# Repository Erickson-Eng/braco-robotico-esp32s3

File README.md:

# Disciplina de prototipagem

Projeto de desenvolvimento de braço róbotico realizado no fusion 360 no qual consiste em criar um braço com uma lâmina acoplada capaz de realizar a manutenção da lavoura fazendo a retirada de fungos e ou também realizar a retirada de algumas frutas como por exemplo a uva.

## Diretorios

- [Arquivos 3D](https://github.com/Erickson-Eng/braco-robotico-esp32s3/tree/main/modelos_3d/componentes-3d)
- [Arquivos F3D](https://github.com/Erickson-Eng/braco-robotico-esp32s3/tree/main/modelos_3d/componentes-f3d)
- [Arquivos STL](https://github.com/Erickson-Eng/braco-robotico-esp32s3/tree/main/modelos_3d/componentes-stl)

## Grupo 7

### Alunos

- Erickson Tulio Rodrigues Azevedo
- Arthur Venancio Furtado Fialho
- Mozart Lima Nascimento

### Professor

- Alexandre Sales Vasconcelos

## Braço robótico

Componentes para construção do braço róbotico.

### Base do braço

### Tampa de conexão entre base e haste

### Haste de conexão com a tampa

### Engrenagem conectora com haste

### Haste de conexão com a lâmina

### Lista de materias

Nome | Referência | Tipo
-----|------------|--------
Stepper Motor | 6627T54 | Motor
Precision Knife Blades | 38995A84_Trade No. 28 | Lâmina

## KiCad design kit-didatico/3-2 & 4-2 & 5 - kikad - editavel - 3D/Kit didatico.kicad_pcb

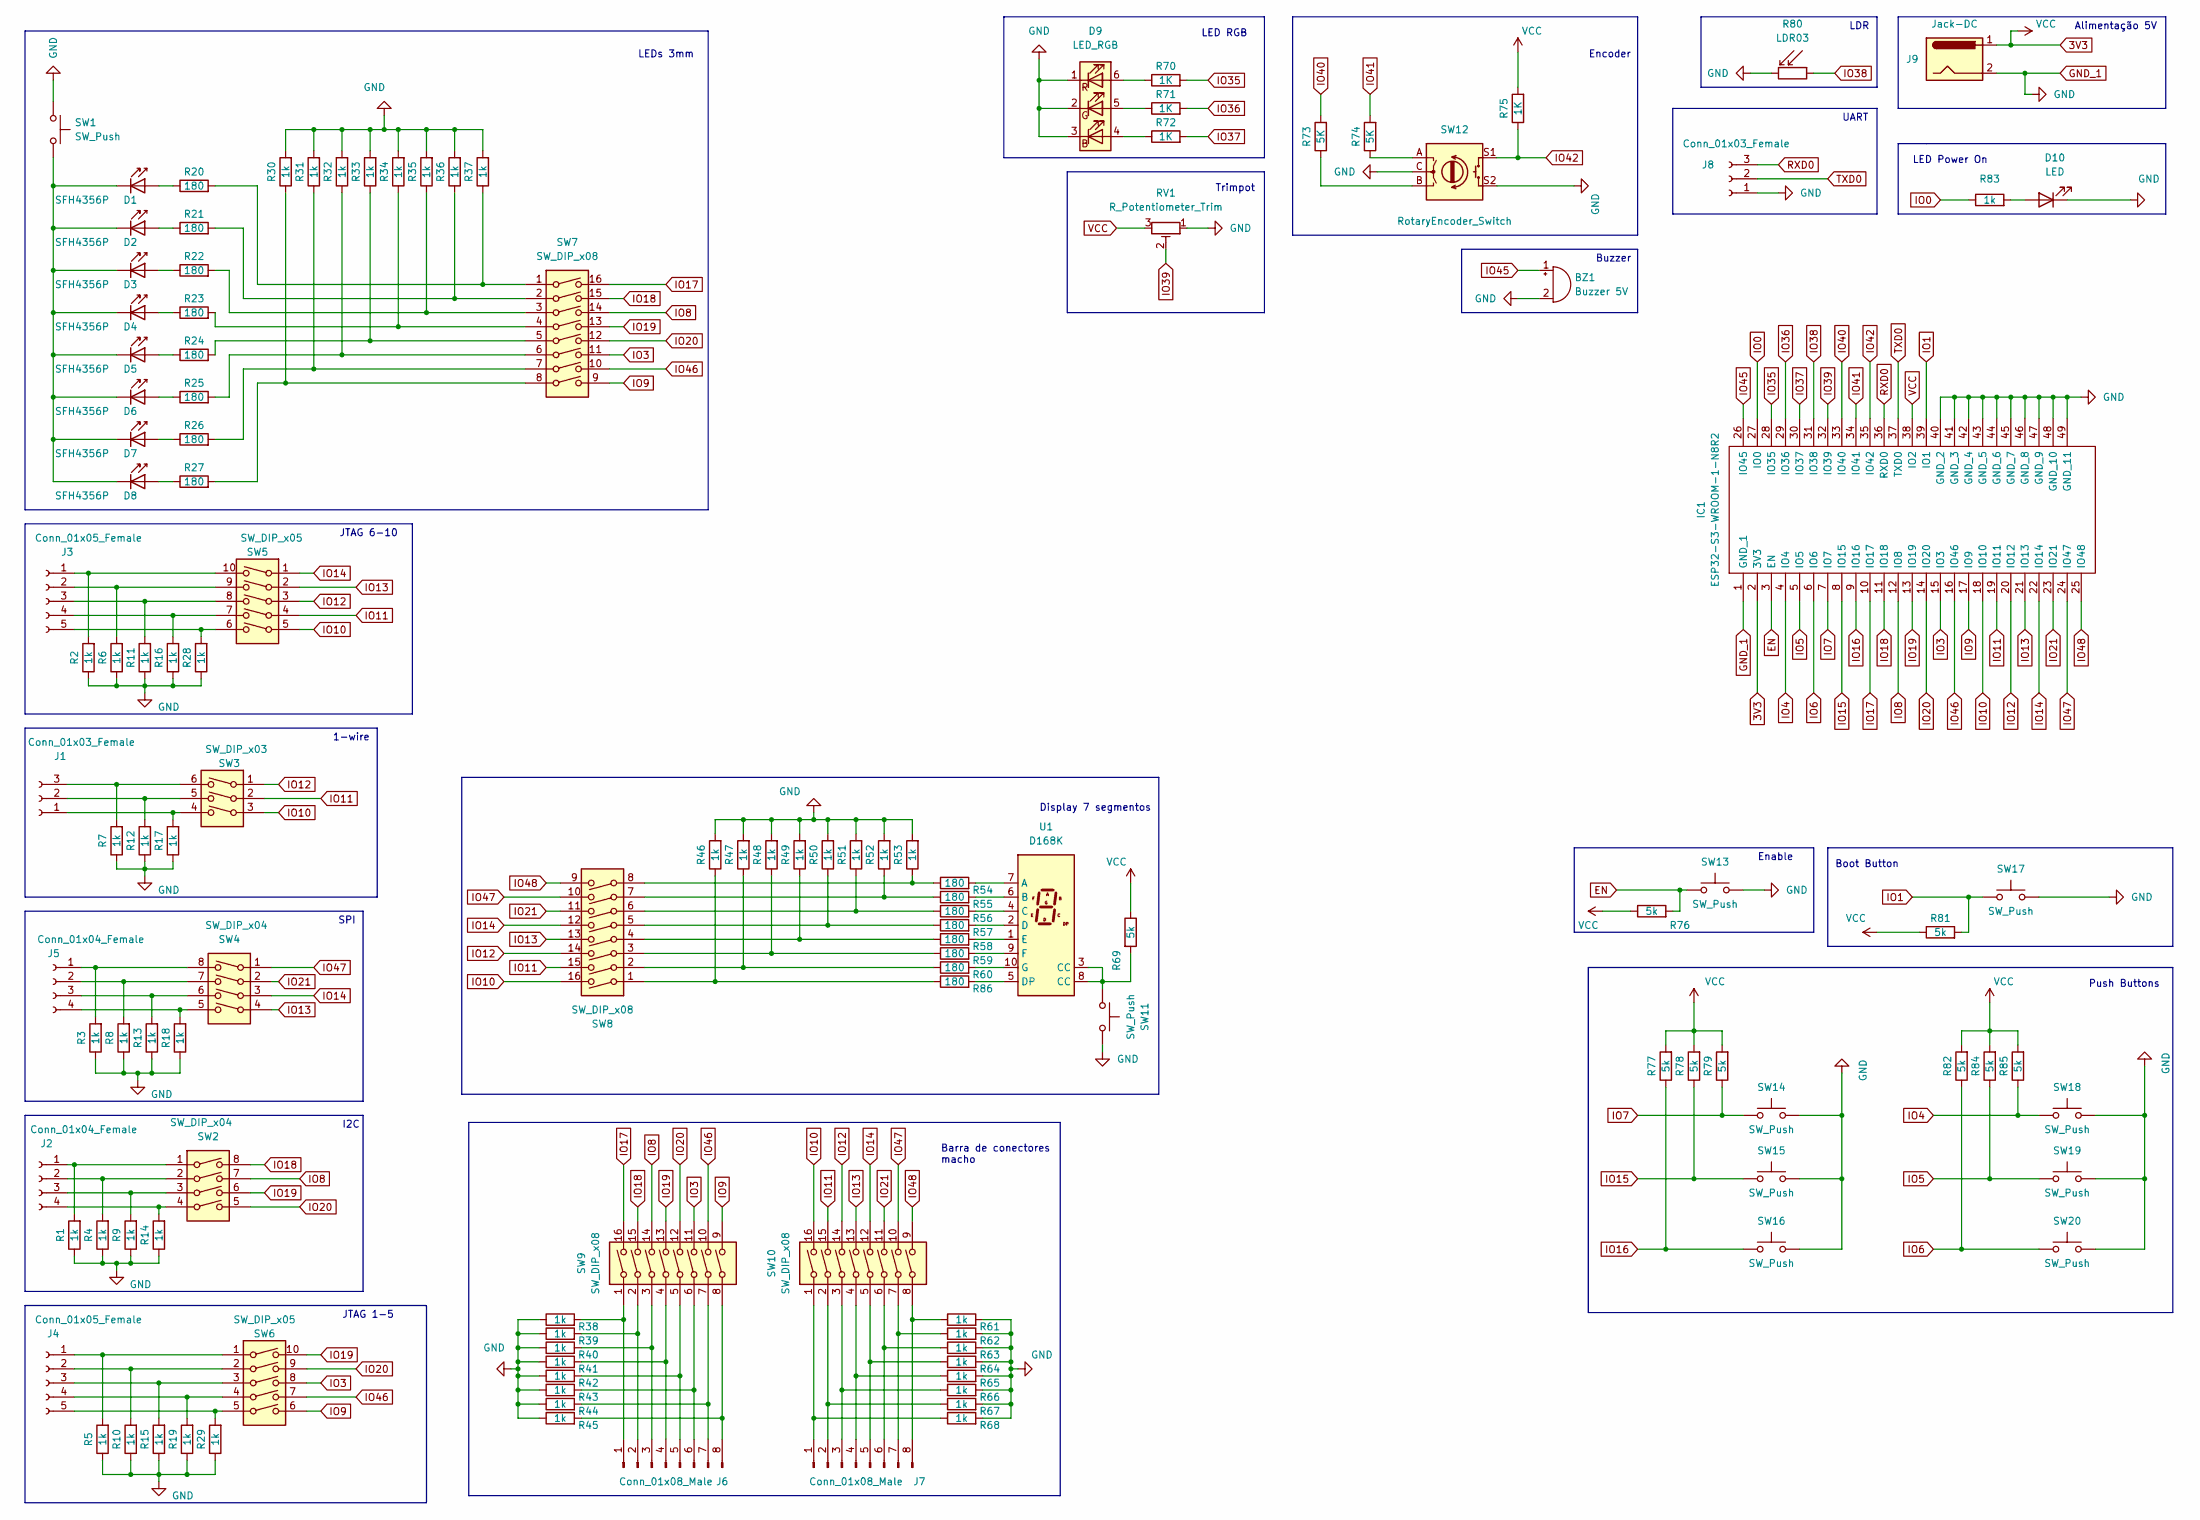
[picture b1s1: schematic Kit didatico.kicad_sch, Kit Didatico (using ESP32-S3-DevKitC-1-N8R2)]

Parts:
BZ1: Buzzer 5V; Buzzer_12x9.5RM7.6
D1, D2, D3, D4, D5, D6, D7, D8: SFH4356P; LED_D3.0mm_IRBlack
D9: LED_RGB; LED_RGB_5050-6
D10: LED; LED_D3.0mm_IRBlack
IC1: ESP32-S3-WROOM-1-N8R2; ESP32S3WROOM1N8R2; Manufacturer_Part_Number ESP32-S3-WROOM-1-N8R2; Mouser Part Number 356-ESP32-S3WRM1N8R2
J1, J8: Conn_01x03_Female; PinSocket_1x03_P2.54mm_Vertical
J2, J5: Conn_01x04_Female; PinSocket_1x04_P2.54mm_Vertical
J3, J4: Conn_01x05_Female; PinSocket_1x05_P2.54mm_Vertical
J6, J7: Conn_01x08_Male; PinHeader_1x08_P2.54mm_Vertical
J9: Jack-DC; BarrelJack_SwitchcraftConxall_RAPC10U_Horizontal
R1, R2, R3, R4, R5, R6, R7, R8, R9, R10, R11, R12, R13, R14, R15, R16, R17, R18, R19, R28, R29, R30, R31, R32, R33, R34, R35, R36, R37, R38, R39, R40, R41, R42, R43, R44, R45, R46, R47, R48, R49, R50, R51, R52, R53, R61, R62, R63, R64, R65, R66, R67, R68, R83: 1k; R_Axial_DIN0204_L3.6mm_D1.6mm_P5.08mm_Horizontal
R20, R21, R22, R23, R24, R25, R26, R27, R54, R55, R56, R57, R58, R59, R60, R86: 180; R_Axial_DIN0204_L3.6mm_D1.6mm_P5.08mm_Horizontal
R69, R76, R77, R78, R79, R81, R82, R84, R85: 5k; R_Axial_DIN0204_L3.6mm_D1.6mm_P5.08mm_Horizontal
R70, R71, R72, R75: 1K; R_Axial_DIN0204_L3.6mm_D1.6mm_P5.08mm_Horizontal
R73, R74: 5K; R_Axial_DIN0204_L3.6mm_D1.6mm_P5.08mm_Horizontal
R80: LDR03; R_LDR_10x8.5mm_P7.6mm_Vertical
RV1: R_Potentiometer_Trim; Potentiometer_ACP_CA9-V10_Vertical
SW1, SW11, SW13, SW14, SW15, SW16, SW17, SW18, SW19, SW20: SW_Push; SW_CW_GPTS203211B
SW2, SW4: SW_DIP_x04; SW_DIP_SPSTx04_Slide_6.7x11.72mm_W6.73mm_P2.54mm_LowProfile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
SW3: SW_DIP_x03; SW_DIP_SPSTx03_Slide_6.7x9.18mm_W6.73mm_P2.54mm_LowProfile_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
SW5, SW6: SW_DIP_x05; SW_DIP_SPSTx05_Slide_6.7x14.26mm_W6.73mm_P2.54mm_LowProfile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
SW7, SW8, SW9, SW10: SW_DIP_x08; SW_DIP_SPSTx08_Slide_6.7x21.88mm_W6.73mm_P2.54mm_LowProfile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
SW12: RotaryEncoder_Switch
U1: D168K; D1X8K

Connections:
3V3: IC1.2 (3V3), IC1.38 (IO2), J9.1, R69.1, R75.2, R76.1, R77.2, R78.2, R79.2, R81.1, R82.2, R84.2, R85.2, RV1.3
EN: IC1.3 (EN), R76.2, SW13.1
GND_1: BZ1.2 (+), D9.1 (RK), D9.2 (GK), D9.3 (BK), D10.1 (K), IC1.1 (GND_1), IC1.40 (GND_2), IC1.41 (GND_3), IC1.42 (GND_4), IC1.43 (GND_5), IC1.44 (GND_6), IC1.45 (GND_7), IC1.46 (GND_8), IC1.47 (GND_9), IC1.48 (GND_10), IC1.49 (GND_11), J8.1, J9.2, R1.1, R2.1, R3.1, R4.1, R5.1, R6.1, R7.1, R8.1, R9.1, R10.1, R11.1, R12.1, R13.1, R14.1, R15.1, R16.1, R17.1, R18.1, R19.1, R28.1, R29.1, R30.2, R31.2, R32.2, R33.2, R34.2, R35.2, R36.2, R37.2, R38.1, R39.1, R40.1, R41.1, R42.1, R43.1, R44.1, R45.1, R46.2, R47.2, R48.2, R49.2, R50.2, R51.2, R52.2, R53.2, R61.2, R62.2, R63.2, R64.2, R65.2, R66.2, R67.2, R68.2, R80.2, RV1.1, SW1.2, SW11.2, SW12.C, SW12.S2, SW13.2, SW14.2, SW15.2, SW16.2, SW17.2, SW18.2, SW19.2, SW20.2
IO0: IC1.27 (IO0), R83.1
IO1: IC1.39 (IO1), R81.2, SW17.1
IO3: IC1.15 (IO3), SW6.8, SW7.11, SW9.11
IO4: IC1.4 (IO4), R85.1, SW18.1
IO5: IC1.5 (IO5), R84.1, SW19.1
IO6: IC1.6 (IO6), R82.1, SW20.1
IO7: IC1.7 (IO7), R79.1, SW14.1
IO8: IC1.12 (IO8), SW2.7, SW7.14, SW9.14
IO9: IC1.17 (IO9), SW6.6, SW7.9, SW9.9
IO10: IC1.18 (IO10), SW3.3, SW5.5, SW8.16, SW10.16
IO11: IC1.19 (IO11), SW3.2, SW5.4, SW8.15, SW10.15
IO12: IC1.20 (IO12), SW3.1, SW5.3, SW8.14, SW10.14
IO13: IC1.21 (IO13), SW4.4, SW5.2, SW8.13, SW10.13
IO14: IC1.22 (IO14), SW4.3, SW5.1, SW8.12, SW10.12
IO15: IC1.8 (IO15), R78.1, SW15.1
IO16: IC1.9 (IO16), R77.1, SW16.1
IO17: IC1.10 (IO17), SW7.16, SW9.16
IO18: IC1.11 (IO18), SW2.8, SW7.15, SW9.15
IO19: IC1.13 (IO19), SW2.6, SW6.10, SW7.13, SW9.13
IO20: IC1.14 (IO20), SW2.5, SW6.9, SW7.12, SW9.12
IO21: IC1.23 (IO21), SW4.2, SW8.11, SW10.11
IO35: IC1.28 (IO35), R70.2
IO36: IC1.29 (IO36), R71.2
IO37: IC1.30 (IO37), R72.2
IO38: IC1.31 (IO38), R80.1
IO39: IC1.32 (IO39), RV1.2
IO40: IC1.33 (IO40), R73.2
IO41: IC1.34 (IO41), R74.2
IO42: IC1.35 (IO42), R75.1, SW12.S1
IO45: BZ1.1 (-), IC1.26 (IO45)
IO46: IC1.16 (IO46), SW6.7, SW7.10, SW9.10
IO47: IC1.24 (IO47), SW4.1, SW8.10, SW10.10
IO48: IC1.25 (IO48), SW8.9, SW10.9
unnamed: D1.1 (K), D2.1 (K), D3.1 (K), D4.1 (K), D5.1 (K), D6.1 (K), D7.1 (K), D8.1 (K), SW1.1
unnamed: D1.2 (A), R20.1
unnamed: D2.2 (A), R21.1
unnamed: D3.2 (A), R22.1
unnamed: D4.2 (A), R23.1
unnamed: D5.2 (A), R24.1
unnamed: D6.2 (A), R25.1
unnamed: D7.2 (A), R26.1
unnamed: D8.2 (A), R27.1
unnamed: D9.4 (BA), R72.1
unnamed: D9.5 (GA), R71.1
unnamed: D9.6 (RA), R70.1
unnamed: D10.2 (A), R83.2
unnamed: J1.1, R17.2, SW3.4
unnamed: J1.2, R12.2, SW3.5
unnamed: J1.3, R7.2, SW3.6
unnamed: J2.1, R1.2, SW2.1
unnamed: J2.2, R4.2, SW2.2
unnamed: J2.3, R9.2, SW2.3
unnamed: J2.4, R14.2, SW2.4
unnamed: J3.1, R2.2, SW5.10
unnamed: J3.2, R6.2, SW5.9
unnamed: J3.3, R11.2, SW5.8
unnamed: J3.4, R16.2, SW5.7
unnamed: J3.5, R28.2, SW5.6
unnamed: J4.1, R5.2, SW6.1
unnamed: J4.2, R10.2, SW6.2
unnamed: J4.3, R15.2, SW6.3
unnamed: J4.4, R19.2, SW6.4
unnamed: J4.5, R29.2, SW6.5
unnamed: J5.1, R3.2, SW4.8
unnamed: J5.2, R8.2, SW4.7
unnamed: J5.3, R13.2, SW4.6
unnamed: J5.4, R18.2, SW4.5
unnamed: J6.1, R38.2, SW9.1
unnamed: J6.2, R39.2, SW9.2
unnamed: J6.3, R40.2, SW9.3
unnamed: J6.4, R41.2, SW9.4
unnamed: J6.5, R42.2, SW9.5
unnamed: J6.6, R43.2, SW9.6
unnamed: J6.7, R44.2, SW9.7
unnamed: J6.8, R45.2, SW9.8
unnamed: J7.1, R68.1, SW10.1
unnamed: J7.2, R67.1, SW10.2
unnamed: J7.3, R66.1, SW10.3
unnamed: J7.4, R65.1, SW10.4
unnamed: J7.5, R64.1, SW10.5
unnamed: J7.6, R63.1, SW10.6
unnamed: J7.7, R62.1, SW10.7
unnamed: J7.8, R61.1, SW10.8
unnamed: R20.2, R37.1, SW7.1
unnamed: R21.2, R36.1, SW7.2
unnamed: R22.2, R35.1, SW7.3
unnamed: R23.2, R34.1, SW7.4
unnamed: R24.2, R33.1, SW7.5
unnamed: R25.2, R32.1, SW7.6
unnamed: R26.2, R31.1, SW7.7
unnamed: R27.2, R30.1, SW7.8
unnamed: R46.1, R86.1, SW8.1
unnamed: R47.1, R60.1, SW8.2
unnamed: R48.1, R59.1, SW8.3
unnamed: R49.1, R58.1, SW8.4
unnamed: R50.1, R57.1, SW8.5
unnamed: R51.1, R56.1, SW8.6
unnamed: R52.1, R55.1, SW8.7
unnamed: R53.1, R54.1, SW8.8
unnamed: R54.2, U1.7 (A)
unnamed: R55.2, U1.6 (B)
unnamed: R56.2, U1.4 (C)
unnamed: R57.2, U1.2 (D)
unnamed: R58.2, U1.1 (E)
unnamed: R59.2, U1.9 (F)
unnamed: R60.2, U1.10 (G)
unnamed: R69.2, SW11.1, U1.3 (CC), U1.8 (CC)
unnamed: R73.1, SW12.B
unnamed: R74.1, SW12.A
unnamed: R86.2, U1.5 (DP)
RXD0: IC1.36 (RXD0), J8.3
TXD0: IC1.37 (TXD0), J8.2

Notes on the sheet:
Boot Button
LEDs 3mm
Buzzer
LED RGB
I2C
Alimentação 5V
1-wire
SPI
Barra de conectores macho
Encoder
Display 7 segmentos
JTAG 6-10
UART
Trimpot
Push Buttons
Enable
LDR
LED Power On
JTAG 1-5

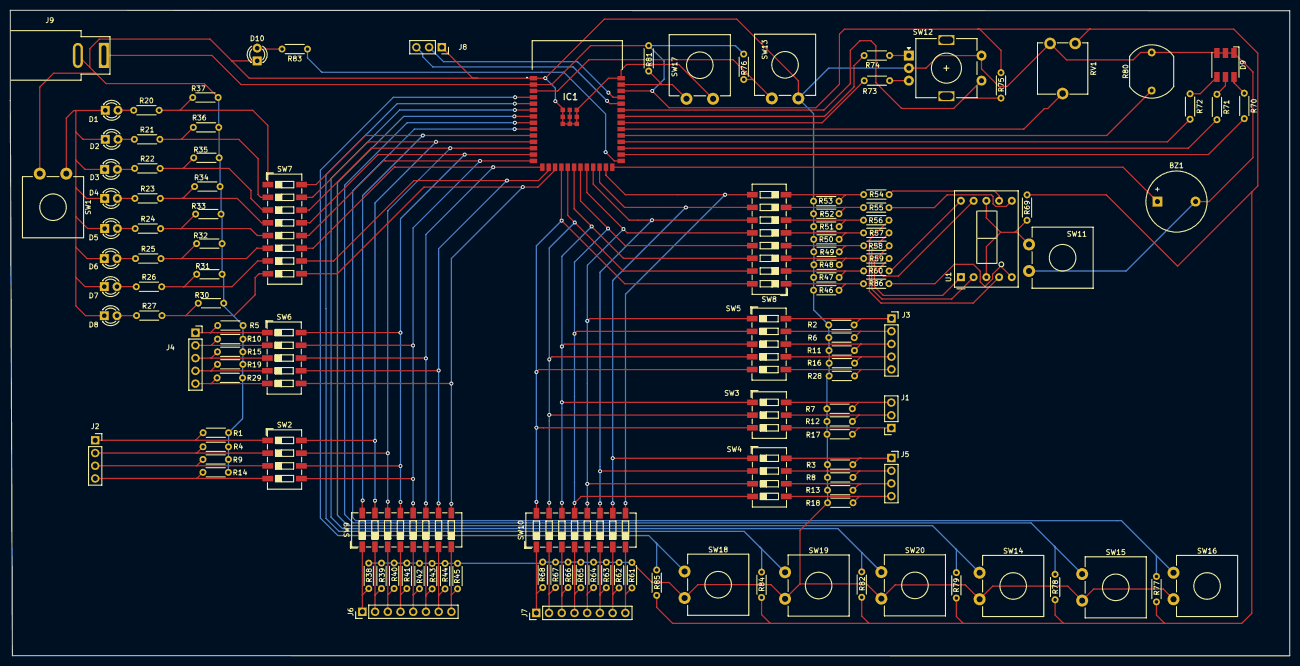
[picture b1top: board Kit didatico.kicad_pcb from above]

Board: 2 copper layers, 255.4 x 128.8 mm, 129 parts (0 on the bottom side), 115 nets.

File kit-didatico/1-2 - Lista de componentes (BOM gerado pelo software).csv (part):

"Source:","/home/arthurvff/IFPB/Prototipagem/Kit didatico/Kit didatico/Kit didatico.kicad_sch"
"Date:","ter 31 mai 2022 21:11:52"
"Tool:","Eeschema 6.0.4-6f826c9f35~116~ubuntu20.04.1"
"Generator:","/usr/share/kicad/plugins/bom_csv_grouped_by_value.py"
"Component Count:","129"

"Individual Components:"

"Item","Qty","Reference(s)","Value","LibPart","Footprint","Datasheet","Description","Height","Manufacturer_Name","Manufacturer_Part_Number","Mouser Part Number","Mouser Price/Stock"
"","","BZ1","Buzzer 5V","Device:Buzzer","Buzzer_Beeper:Buzzer_12x9.5RM7.6","~","","","","","",""
"","","D1","SFH4356P","LED:SFH4356P","LED_THT:LED_D3.0mm_IRBlack","http://www.osram-os.com/Graphics/XPic5/00181708_0.pdf","","","","","",""
"","","D2","SFH4356P","LED:SFH4356P","LED_THT:LED_D3.0mm_IRBlack","http://www.osram-os.com/Graphics/XPic5/00181708_0.pdf","","","","","",""
"","","D3","SFH4356P","LED:SFH4356P","LED_THT:LED_D3.0mm_IRBlack","http://www.osram-os.com/Graphics/XPic5/00181708_0.pdf","","","","","",""
"","","D4","SFH4356P","LED:SFH4356P","LED_THT:LED_D3.0mm_IRBlack","http://www.osram-os.com/Graphics/XPic5/00181708_0.pdf","","","","","",""
"","","D5","SFH4356P","LED:SFH4356P","LED_THT:LED_D3.0mm_IRBlack","http://www.osram-os.com/Graphics/XPic5/00181708_0.pdf","","","","","",""
"","","D6","SFH4356P","LED:SFH4356P","LED_THT:LED_D3.0mm_IRBlack","http://www.osram-os.com/Graphics/XPic5/00181708_0.pdf","","","","","",""
"","","D7","SFH4356P","LED:SFH4356P","LED_THT:LED_D3.0mm_IRBlack","http://www.osram-os.com/Graphics/XPic5/00181708_0.pdf","","","","","",""
"","","D8","SFH4356P","LED:SFH4356P","LED_THT:LED_D3.0mm_IRBlack","http://www.osram-os.com/Graphics/XPic5/00181708_0.pdf","","","","","",""
"","","D9","LED_RGB","Device:LED_RGB","LED_SMD:LED_RGB_5050-6","~","","","","","",""
"","","D10","LED","Device:LED","LED_THT:LED_D3.0mm_IRBlack","~","","","","","",""
"","","IC1","ESP32-S3-WROOM-1-N8R2","ESP32-S3-WROOM-1-N8R2:ESP32-S3-WROOM-1-N8R2","ESP32S3WROOM:ESP32S3WROOM1N8R2","https://www.mouser.com/catalog/specsheets/Espressif_ESP32_S3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","WiFi Modules - 802.11 (Engineering Samples Only) SMD Module, ESP32-S3R2, 2 MB PSRAM, 8 MB SPI Flash, PCB Antenna ,,","3.25","Espressif Systems","ESP32-S3-WROOM-1-N8R2","356-ESP32-S3WRM1N8R2","https://www.mouser.co.uk/ProductDetail/Espressif-Systems/ESP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"
"","","J1","Conn_01x03_Female","Connector:Conn_01x03_Female","Connector_PinSocket_2.54mm:PinSocket_1x03_P2.54mm_Vertical","~","","","","","",""
"","","J2","Conn_01x04_Female","Connector:Conn_01x04_Female","Connector_PinSocket_2.54mm:PinSocket_1x04_P2.54mm_Vertical","~","","","","","",""
"","","J3","Conn_01x05_Female","Connector:Conn_01x05_Female","Connector_PinSocket_2.54mm:PinSocket_1x05_P2.54mm_Vertical","~","","","","","",""
"","","J4","Conn_01x05_Female","Connector:Conn_01x05_Female","Connector_PinSocket_2.54mm:PinSocket_1x05_P2.54mm_Vertical","~","","","","","",""
"","","J5","Conn_01x04_Female","Connector:Conn_01x04_Female","Connector_PinSocket_2.54mm:PinSocket_1x04_P2.54mm_Vertical","~","","","","","",""
"","","J6","Conn_01x08_Male","Connector:Conn_01x08_Male","Connector_PinHeader_2.54mm:PinHeader_1x08_P2.54mm_Vertical","~","","","","","",""
"","","J7","Conn_01x08_Male","Connector:Conn_01x08_Male","Connector_PinHeader_2.54mm:PinHeader_1x08_P2.54mm_Vertical","~","","","","","",""
"","","J8","Conn_01x03_Female","Connector:Conn_01x03_Female","Connector_PinSocket_2.54mm:PinSocket_1x03_P2.54mm_Vertical","~","","","","","",""
"","","J9","Jack-DC","Connector:Jack-DC","Connector_BarrelJack:BarrelJack_SwitchcraftConxall_RAPC10U_Horizontal","~","","","","","",""
"","","R1","1k","Device:R","Resistor_THT:R_Axial_DIN0204_L3.6mm_D1.6mm_P5.08mm_Horizontal","~","","","","","",""
"","","R2","1k","Device:R","Resistor_THT:R_Axial_DIN0204_L3.6mm_D1.6mm_P5.08mm_Horizontal","~","","","","","",""
"","","R3","1k","Device:R","Resistor_THT:R_Axial_DIN0204_L3.6mm_D1.6mm_P5.08mm_Horizontal","~","","","","","",""
"","","R4","1k","Device:R","Resistor_THT:R_Axial_DIN0204_L3.6mm_D1.6mm_P5.08mm_Horizontal","~","","","","","",""
"","","R5","1k","Device:R","Resistor_THT:R_Axial_DIN0204_L3.6mm_D1.6mm_P5.08mm_Horizontal","~","","","","","",""
"","","R6","1k","Device:R","Resistor_THT:R_Axial_DIN0204_L3.6mm_D1.6mm_P5.08mm_Horizontal","~","","","","","",""
"","","R7","1k","Device:R","Resistor_THT:R_Axial_DIN0204_L3.6mm_D1.6mm_P5.08mm_Horizontal","~","","","","","",""
"","","R8","1k","Device:R","Resistor_THT:R_Axial_DIN0204_L3.6mm_D1.6mm_P5.08mm_Horizontal","~","","","","","",""
"","","R9","1k","Device:R","Resistor_THT:R_Axial_DIN0204_L3.6mm_D1.6mm_P5.08mm_Horizontal","~","","","","","",""
"","","R10","1k","Device:R","Resistor_THT:R_Axial_DIN0204_L3.6mm_D1.6mm_P5.08mm_Horizontal","~","","","","","",""
"","","R11","1k","Device:R","Resistor_THT:R_Axial_DIN0204_L3.6mm_D1.6mm_P5.08mm_Horizontal","~","","","","","",""
"","","R12","1k","Device:R","Resistor_THT:R_Axial_DIN0204_L3.6mm_D1.6mm_P5.08mm_Horizontal","~","","","","","",""
"","","R13","1k","Device:R","Resistor_THT:R_Axial_DIN0204_L3.6mm_D1.6mm_P5.08mm_Horizontal","~","","","","","",""
"","","R14","1k","Device:R","Resistor_THT:R_Axial_DIN0204_L3.6mm_D1.6mm_P5.08mm_Horizontal","~","","","","","",""
"","","R15","1k","Device:R","Resistor_THT:R_Axial_DIN0204_L3.6mm_D1.6mm_P5.08mm_Horizontal","~","","","","","",""
"","","R16","1k","Device:R","Resistor_THT:R_Axial_DIN0204_L3.6mm_D1.6mm_P5.08mm_Horizontal","~","","","","","",""
"","","R17","1k","Device:R","Resistor_THT:R_Axial_DIN0204_L3.6mm_D1.6mm_P5.08mm_Horizontal","~","","","","","",""
"","","R18","1k","Device:R","Resistor_THT:R_Axial_DIN0204_L3.6mm_D1.6mm_P5.08mm_Horizontal","~","","","","","",""
"","","R19","1k","Device:R","Resistor_THT:R_Axial_DIN0204_L3.6mm_D1.6mm_P5.08mm_Horizontal","~","","","","","",""
"","","R20","180","Device:R","Resistor_THT:R_Axial_DIN0204_L3.6mm_D1.6mm_P5.08mm_Horizontal","~","","","","","",""
"","","R21","180","Device:R","Resistor_THT:R_Axial_DIN0204_L3.6mm_D1.6mm_P5.08mm_Horizontal","~","","","","","",""
"","","R22","180","Device:R","Resistor_THT:R_Axial_DIN0204_L3.6mm_D1.6mm_P5.08mm_Horizontal","~","","","","","",""
"","","R23","180","Device:R","Resistor_THT:R_Axial_DIN0204_L3.6mm_D1.6mm_P5.08mm_Horizontal","~","","","","","",""
"","","R24","180","Device:R","Resistor_THT:R_Axial_DIN0204_L3.6mm_D1.6mm_P5.08mm_Horizontal","~","","","","","",""
"","","R25","180","Device:R","Resistor_THT:R_Axial_DIN0204_L3.6mm_D1.6mm_P5.08mm_Horizontal","~","","","","","",""
"","","R26","180","Device:R","Resistor_THT:R_Axial_DIN0204_L3.6mm_D1.6mm_P5.08mm_Horizontal","~","","","","","",""
"","","R27","180","Device:R","Resistor_THT:R_Axial_DIN0204_L3.6mm_D1.6mm_P5.08mm_Horizontal","~","","","","","",""
"","","R28","1k","Device:R","Resistor_THT:R_Axial_DIN0204_L3.6mm_D1.6mm_P5.08mm_Horizontal","~","","","","","",""
"","","R29","1k","Device:R","Resistor_THT:R_Axial_DIN0204_L3.6mm_D1.6mm_P5.08mm_Horizontal","~","","","","","",""
"","","R30","1k","Device:R","Resistor_THT:R_Axial_DIN0204_L3.6mm_D1.6mm_P5.08mm_Horizontal","~","","","","","",""
"","","R31","1k","Device:R","Resistor_THT:R_Axial_DIN0204_L3.6mm_D1.6mm_P5.08mm_Horizontal","~","","","","","",""
"","","R32","1k","Device:R","Resistor_THT:R_Axial_DIN0204_L3.6mm_D1.6mm_P5.08mm_Horizontal","~","","","","","",""
"","","R33","1k","Device:R","Resistor_THT:R_Axial_DIN0204_L3.6mm_D1.6mm_P5.08mm_Horizontal","~","","","","","",""
"","","R34","1k","Device:R","Resistor_THT:R_Axial_DIN0204_L3.6mm_D1.6mm_P5.08mm_Horizontal","~","","","","","",""
"","","R35","1k","Device:R","Resistor_THT:R_Axial_DIN0204_L3.6mm_D1.6mm_P5.08mm_Horizontal","~","","","","","",""
"","","R36","1k","Device:R","Resistor_THT:R_Axial_DIN0204_L3.6mm_D1.6mm_P5.08mm_Horizontal","~","","","","","",""
"","","R37","1k","Device:R","Resistor_THT:R_Axial_DIN0204_L3.6mm_D1.6mm_P5.08mm_Horizontal","~","","","","","",""
"","","R38","1k","Device:R","Resistor_THT:R_Axial_DIN0204_L3.6mm_D1.6mm_P5.08mm_Horizontal","~","","","","","",""
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
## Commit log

2022-07-26 Readme + estrutura de pastas
2022-08-02 kit-didatico
2022-08-24 atualização do readme e do arquivo relatorio
2022-08-28 Refatoração do projeto do braço 3d realizando melhorias
2022-08-28 Atualização readme
2022-08-28 adicionado arquivo da vista e uma pasta para os arquivos relativos ao fatiador
